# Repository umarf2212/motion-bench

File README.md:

# Motion Bench

Four-button Bluetooth air mouse for macOS. ESP32-C3 Super Mini, MPU-6050, and a browser-based 3D motion viewer.

## Wire and flash

Unplug USB before wiring. Use the ESP32 pin labels.

| MPU-6050 | ESP32-C3 | ESP32-WROOM (USB viewer) |
| --- | --- | --- |
| VCC | 3V3 | 3V3 |
| GND | GND | GND |
| SDA | GPIO4 | GPIO21 |
| SCL | GPIO5 | GPIO22 |

Leave `INT`, `XDA`, and `XCL` open. The firmware checks both I²C addresses. Tie `AD0` to GND if it would otherwise float.

On the C3, wire each switch between its GPIO and GND. Use one leg from each contact pair on a four-leg switch. Internal pull-ups are enabled.

| GPIO | Control |
| --- | --- |
| GPIO0 | Left-click. Double-tap to double-click. Hold while moving to drag. |
| GPIO1 | Right-click. |
| GPIO6 | Hold to move. Double-tap to toggle movement lock. |
| GPIO7 | Hold to scroll on both axes. Pressing clears movement lock and stops any coast. A sharper flick coasts farther after release. |

Copy [the firmware](micropython/main.py) to `/main.py` on the MicroPython board. Reset and keep the sensor still for calibration.

## Build the Mac app

Run from the repo root on macOS 12+ with Xcode Command Line Tools installed.

```sh
motion_app="mac-client/Motion Bench Bluetooth.app"
mkdir -p "$motion_app/Contents/MacOS"
cp mac-client/Info.plist "$motion_app/Contents/Info.plist"
xcrun swiftc -parse-as-library -O -target "$(uname -m)-apple-macos12.0" \
  mac-client/MotionBench.swift -o "$motion_app/Contents/MacOS/MotionBench"
codesign --force --sign - "$motion_app"
```

1. Open **Motion Bench Bluetooth.app** from `mac-client`. Allow Bluetooth access and click **Connect** to find **MotionC3**.
2. Set the sensor down and click **Enable cursor**. If prompted, allow the app under **System Settings > Privacy & Security > Accessibility**, then retry.
3. Set **Move left**, **Move up**, and **Cursor speed**. Defaults are Z counterclockwise for left and X counterclockwise for up. Scroll uses the same directions.

If the pointer drifts, stop cursor control and re-enable it with the board still. **Stop cursor** or **Esc** in the app disables pointer control.

## Web viewer and tools

- **3D viewer:** Open [index.html](index.html) in desktop Chrome. Choose **Play demo** or **Connect USB**. If USB access is blocked, run `python3 -m http.server 8000 --bind 127.0.0.1` and open [localhost:8000](http://localhost:8000).
- **Web Bluetooth or system cursor:** Run `python3 cursor_helper.py` on macOS and open [127.0.0.1:8765](http://127.0.0.1:8765) in Chrome. Select **MotionC3** under **Connect Bluetooth**. **System cursor** requires macOS Accessibility access.
- **BLE terminal reader:** Install `bleak` and run `python3 bluetooth_reader.py`. Connect one Bluetooth client at a time.
- **Arduino USB stream:** Upload [the ESP32-WROOM sketch](mpu6050_stream/mpu6050_stream.ino) with the Espressif ESP32 board package. Select **ESP32 Dev Module**. Serial runs at 115200 baud.
- **Rev A carrier PCB:** [KiCad and layout files](pcb-design/). Grid checks passed. Verify module fit and run KiCad DRC before fabrication.

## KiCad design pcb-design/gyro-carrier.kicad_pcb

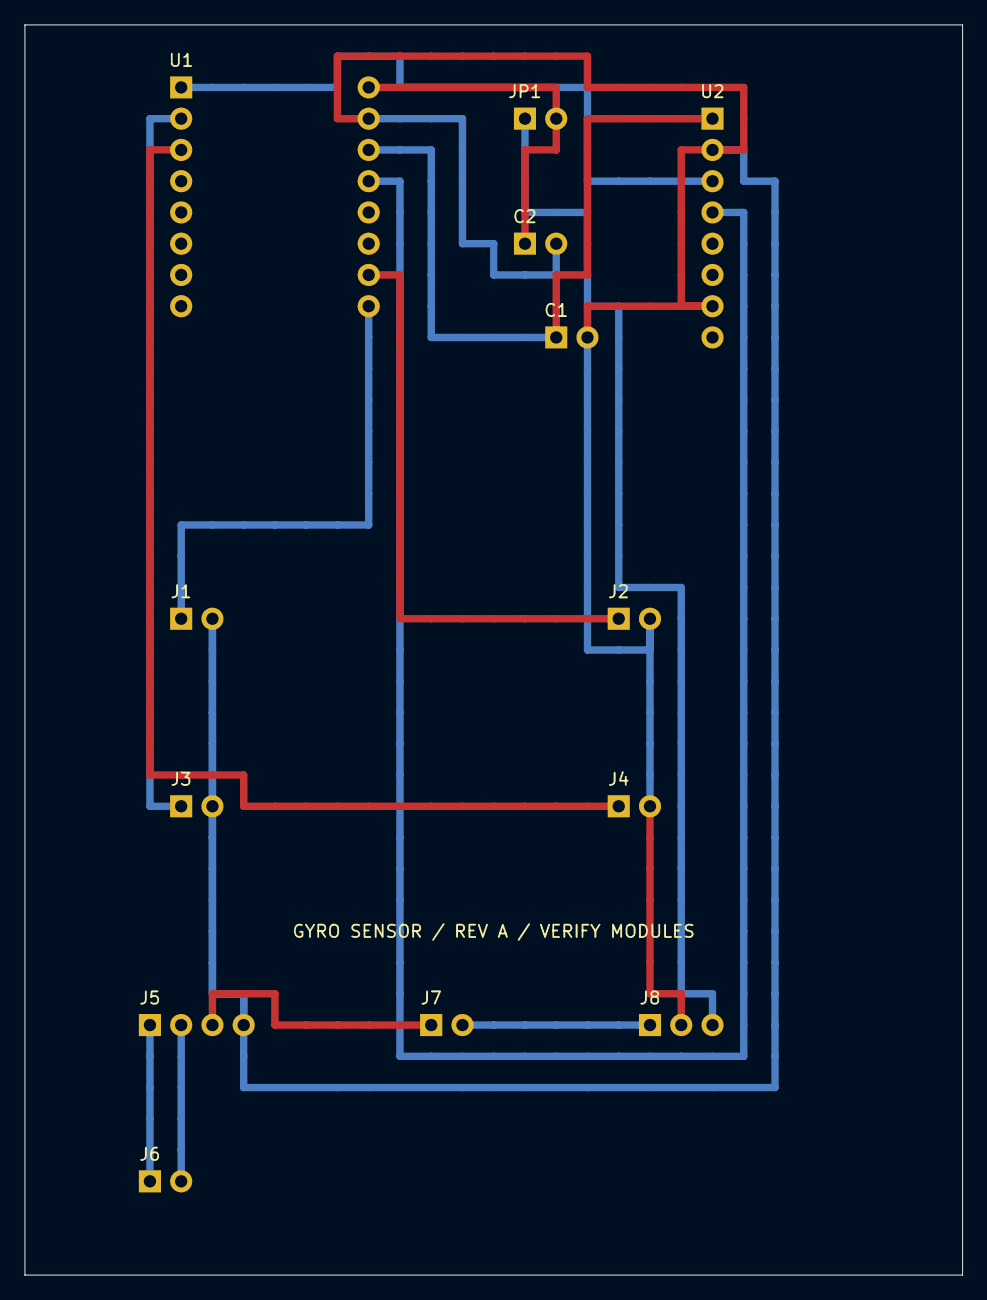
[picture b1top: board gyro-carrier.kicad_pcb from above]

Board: 2 copper layers, 76.2 x 101.6 mm, 13 parts (0 on the bottom side), 14 nets.

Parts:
C1: 100 nF ceramic; C1
C2: 100 µF / 10 V; C2
J1: Left click; J1
J2: Right click; J2
J3: Hold to move; J3
J4: Hold to scroll; J4
J5: Charger interface; J5
J6: Battery connector; J6
J7: Power switch; J7
J8: 5 V regulator interface; J8
JP1: Battery isolation link; JP1
U1: ESP32-C3 SuperMini; U1
U2: MPU-6050 / GY-521; U2

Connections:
BAT_MINUS: J5.2, J6.2
BAT_PLUS: J5.1, J6.1
BOOST_5V: J8.3, JP1.1
GND: C1.2, C2.2, J1.2, J2.2, J3.2, J4.2, J5.4, J8.2, U1.10, U2.2, U2.7
LEFT: J1.1, U1.16
MOVE: J3.1, U1.2
PROTECTED_PLUS: J5.3, J7.1
RIGHT: J2.1, U1.15
SCL: U1.1, U2.3
SCROLL: J4.1, U1.3
SDA: U1.12, U2.4
SWITCHED_BAT: J7.2, J8.1
V3V3: C1.1, U1.11, U2.1
V5: C2.1, JP1.2, U1.9

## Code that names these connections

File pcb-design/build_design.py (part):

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for ref,name,x,y,net in [('J1','Left click',5,19,'LEFT'),('J2','Right click',19,19,'RIGHT'),('J3','Hold to move',5,25,'MOVE'),('J4','Hold to scroll',19,25,'SCROLL')]:
    part(ref,name,[(x,y,'SIG',net),(x+1,y,'GND','GND')],[x-1,y-2,4,4], '2-pin 2.54 mm switch connection, NOT a 4-leg tactile-switch footprint. Wire opposite electrical contacts of your existing switch to these pads; mount switch to suit its measured lead spacing.')
part('J5','Charger interface',[(4+i,32,l,n) for i,(l,n) in enumerate([('B+','BAT_PLUS'),('B−','BAT_MINUS'),('OUT+','PROTECTED_PLUS'),('OUT−','GND')])],[2.5,30,7,8], 'Four separate wires to the printed TP4056 module labels; this is not its physical module footprint. Keep B− separate from OUT−.')
part('J6','Battery connector',[(4,37,'+','BAT_PLUS'),(5,37,'−','BAT_MINUS')],None,'2.54 mm header/wire pads, not a JST-PH footprint. Check polarity. Cell stays off the carrier.')
part('J7','Power switch',[(13,32,'IN','PROTECTED_PLUS'),(14,32,'OUT','SWITCHED_BAT')],None,'External SPST switch via two wires; opens the positive battery feed. OFF for charging and for ESP32 USB.')
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part('JP1','Battery isolation link',[(16,3,'BOOST','BOOST_5V'),(17,3,'C3','V5')],None,'2-pin shunt. REMOVE before plugging USB into the ESP32. No automatic source selection is implemented.')
part('C1','100 nF ceramic',[(17,10,'+','V3V3'),(18,10,'−','GND')],None,'2.54 mm pitch, non-polarized. Across sensor supply.')
part('C2','100 µF / 10 V',[(16,7,'+','V5'),(17,7,'−','GND')],None,'2.54 mm lead pitch electrolytic, diameter <=6.3 mm. Observe polarity.')
nets=list(dict.fromkeys(p['net'] for p in pins if p['net']))
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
